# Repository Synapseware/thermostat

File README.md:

# thermostat
Just a basic thermostat control for one of the bedrooms

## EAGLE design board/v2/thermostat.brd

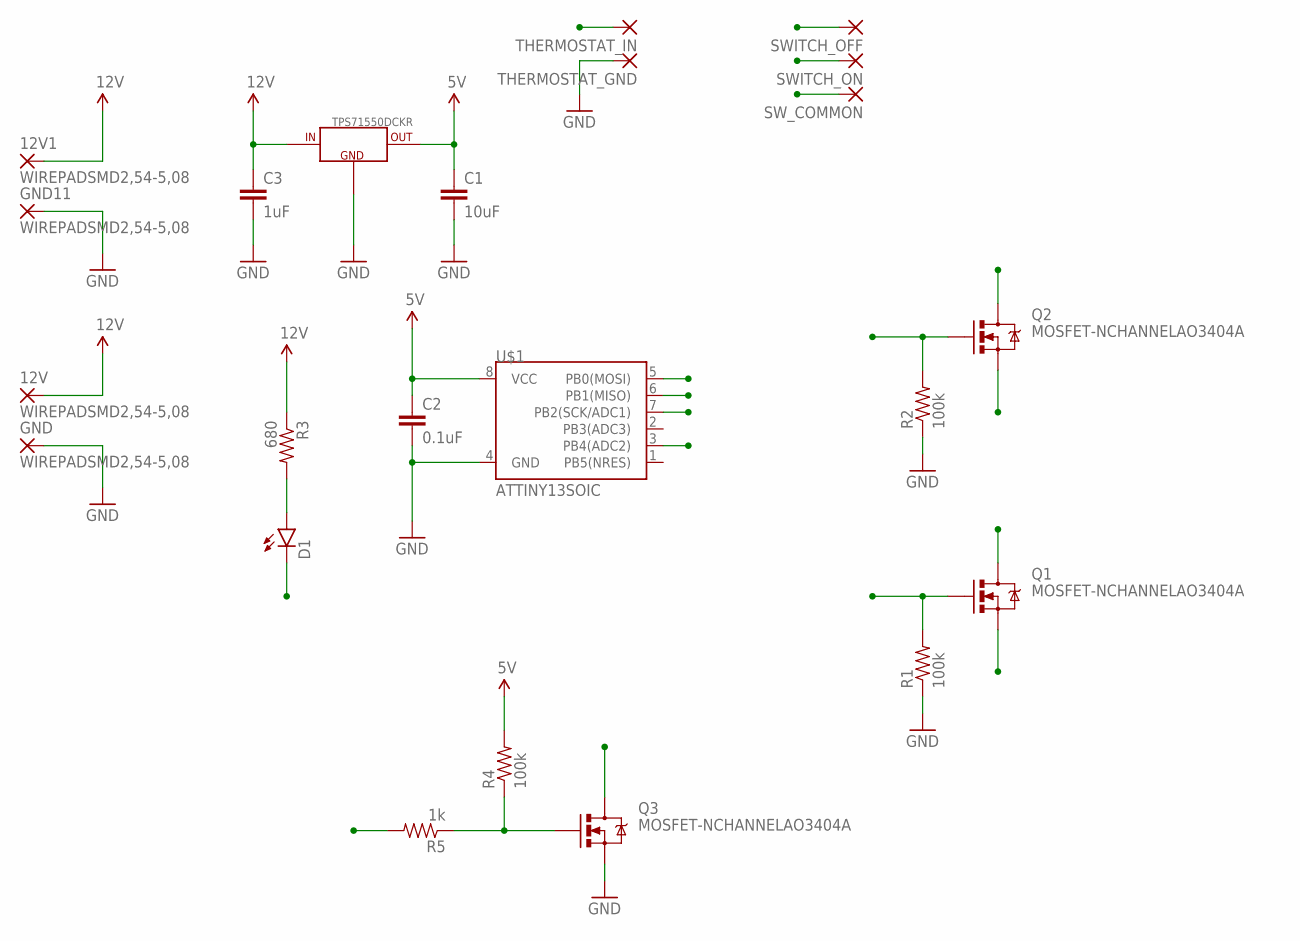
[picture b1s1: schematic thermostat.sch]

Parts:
12V, 12V1: WIREPADSMD2,54-5,08; SMD2,54-5,08
C1: 10uF; 1210
C2: 0.1uF; 0805
C3: 1uF; 1210
D1: LED0603; LED-0603
GND, GND11: WIREPADSMD2,54-5,08; SMD2,54-5,08
Q1, Q2, Q3: MOSFET-NCHANNELAO3404A; SOT23-3
R1, R2, R4: 100k; 0805
R3: 680; 0805
R5: 1k; 0805
SWITCH_OFF: WIREPADSMD2,54-5,08; SMD2,54-5,08
SWITCH_ON: WIREPADSMD2,54-5,08; SMD2,54-5,08
SW_COMMON: WIREPADSMD2,54-5,08; SMD2,54-5,08
THERMOSTAT_GND: WIREPADSMD2,54-5,08; SMD2,54-5,08
THERMOSTAT_IN: WIREPADSMD2,54-5,08; SMD2,54-5,08
TPS71550DCKR: TPS715XX; SC70-5
U$1: ATTINY13SOIC; SO08

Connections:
5V: C1.1, C2.1, R4.2, TPS71550DCKR.5 (OUT), U$1.8 (VCC)
12V: 12V.1, 12V1.1, C3.1, R3.1, TPS71550DCKR.4 (IN)
GND: C1.2, C2.2, C3.2, GND.1, GND11.1, Q3.2 (S), R1.1, R2.1, THERMOSTAT_GND.1, TPS71550DCKR.2 (GND), U$1.4 (GND)
HEAT_OFF: Q2.1 (G), R2.2, U$1.5 (PB0(MOSI))
HEAT_ON: Q1.1 (G), R1.2, U$1.6 (PB1(MISO))
LED: D1.C, U$1.3 (PB4(ADC2))
unnamed: Q3.1 (G), R4.1, R5.1
unnamed: D1.A, R3.2
SENSOR_IN: Q3.3 (D), U$1.7 (PB2(SCK/ADC1))
SWITCH_OFF: Q2.2 (S), SWITCH_OFF.1
SWITCH_ON: Q1.2 (S), SWITCH_ON.1
SW_COMMON: Q1.3 (D), Q2.3 (D), SW_COMMON.1
THERMOSTAT_IN: R5.2, THERMOSTAT_IN.1

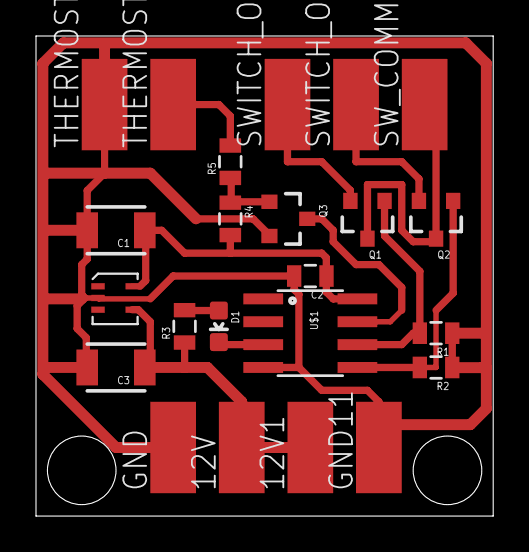
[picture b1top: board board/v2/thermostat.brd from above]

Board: 2 copper layers, 25.4 x 26.7 mm, 23 parts (0 on the bottom side), 13 nets.

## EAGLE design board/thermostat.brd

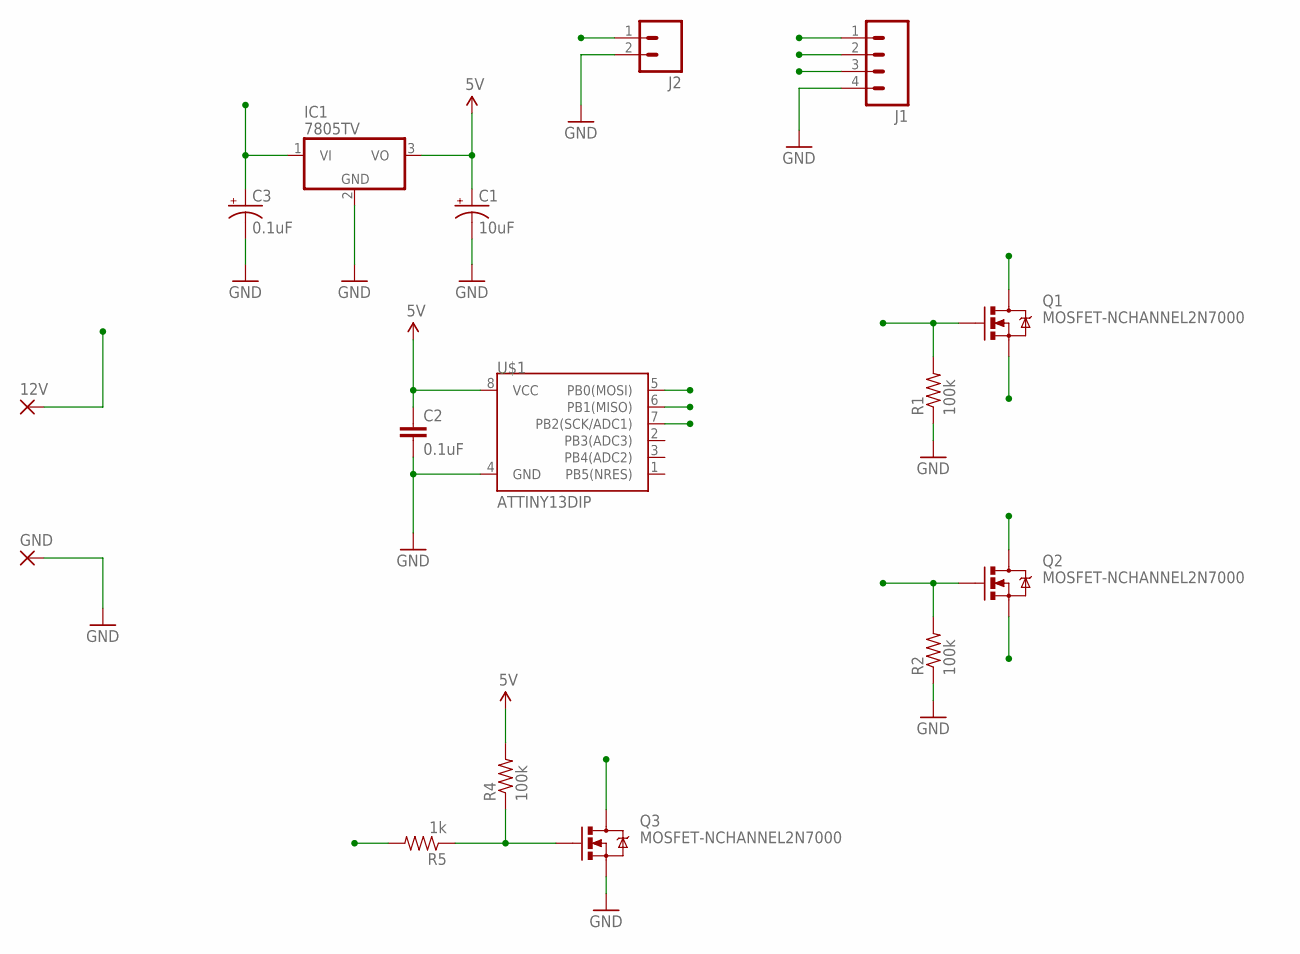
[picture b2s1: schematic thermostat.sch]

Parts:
12V: WIREPAD2,54/0,8; 2,54/0,8
C1: 10uF; CPOL-RADIAL-10UF-25V
C2: 0.1uF; CAP-PTH-SMALLEZ
C3: 0.1uF; CPOL-RADIAL-10UF-25V
GND: WIREPAD2,54/0,8; 2,54/0,8
IC1: 7805TV; TO220V
J1: M04PTH; 1X04
J2: M02PTH; 1X02
Q1, Q2, Q3: MOSFET-NCHANNEL2N7000; TO-92
R1, R2, R4: 100k; AXIAL-0.3
R5: 1k; AXIAL-0.3
U$1: ATTINY13DIP; DIP08

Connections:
5V: C1.1 (+), C2.1, IC1.3 (VO), R4.P$2 (2), U$1.8 (VCC)
12V: 12V.1, C3.1 (+), IC1.1 (VI); also elsewhere on the board
GND: C1.2 (-), C2.2, C3.2 (-), GND.1, IC1.2 (GND), J1.4, J2.2, Q3.1 (S), R1.P$1 (1), R2.P$1 (1), U$1.4 (GND); also elsewhere on the board
HEAT_OFF: Q2.2 (G), R2.P$2 (2), U$1.5 (PB0(MOSI))
HEAT_ON: Q1.2 (G), R1.P$2 (2), U$1.6 (PB1(MISO))
unnamed: Q3.2 (G), R4.P$1 (1), R5.P$1 (1)
SENSOR_IN: Q3.3 (D), U$1.7 (PB2(SCK/ADC1))
SWITCH_OFF: J1.1, Q2.1 (S)
SWITCH_ON: J1.2, Q1.1 (S)
SW_COMMON: J1.3, Q1.3 (D), Q2.3 (D)
THERMOSTAT_IN: J2.1, R5.P$2 (2)

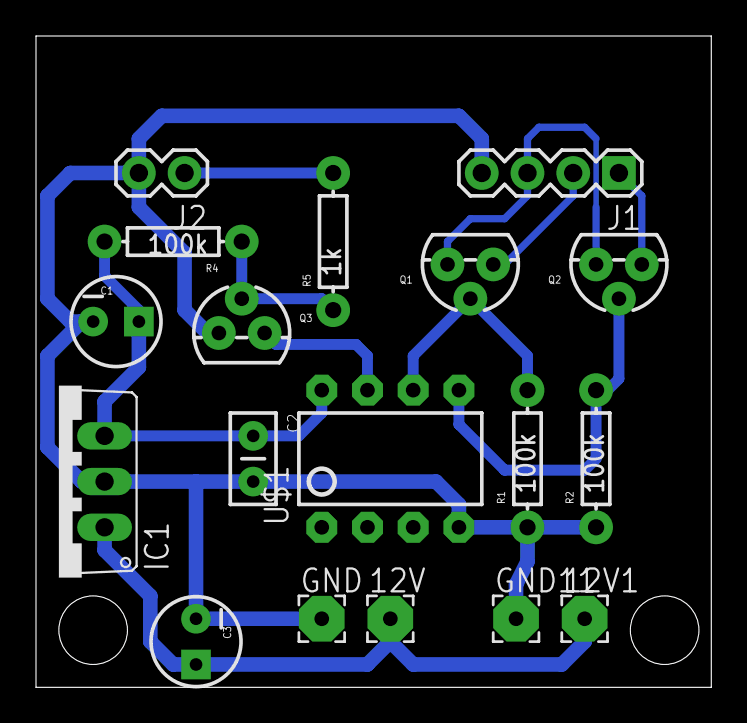
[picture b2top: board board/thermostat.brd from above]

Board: 2 copper layers, 37.5 x 36.2 mm, 18 parts (0 on the bottom side), 11 nets.

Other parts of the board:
12V1: 2,54/0,8
GND11: 2,54/0,8

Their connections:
12V: 12V1.1; also elsewhere on the board
GND: GND11.1; also elsewhere on the board

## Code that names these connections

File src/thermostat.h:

#ifndef __THERMOSTAT__H_
#define __THERMOSTAT__H_


#include <avr/io.h>
#include <avr/interrupt.h>
#include <avr/wdt.h>
#include <util/delay.h>


#define THERMOSTAT_PIN		PB2
#define HEAT_ON				PB1
#define HEAT_OFF			PB0

#define TOGGLE_COUNT		3
#define TOGGLE_ON_DELAY		400
#define TOGGLE_OFF_DELAY	800


#endif

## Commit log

2017-02-05 Thermostat is functional
    Had to fix a problem with the watch dog timer. Apparently, there's a
    bug in wdt.h, so I had to add the disable code manually and not use the
    helper library.
2017-02-05 WIP: Protecting input and creating schematic
2017-02-05 Board layout updates
2017-02-08 Production build & source
    The Thermostat relay board is successfully working in the spare bedroom.
2017-02-08 Adding board dimensions for RadioShack case
    I decided to package this project in a Radio Shack project case for
    expediency. It's likely that it'll never move from this case, and that
    I'll end up mounting this project in a closet somewhere and running a
    wire for the thermostat.
2017-07-15 Adding photos of board
2017-12-27 Misc board updates
2017-12-27 Ignore epf files
2017-12-28 Reorganizing for surface mount version
2017-12-29 SMD layout complete

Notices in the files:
parts and their libraries:
SparkFun-DigitalIC: Licensing: CC v3.0 Share-Alike You are welcome to use this library for commercial purposes.
SparkFun-DiscreteSemi: Licensing: Creative Commons ShareAlike 4.0 International - https://creativecommons.org/licenses/by-sa/4.0
